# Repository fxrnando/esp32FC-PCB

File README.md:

# ESP32FC - PCB for X Quadcopter Drones

This repository contains the PCB designs and hardware documentation for a flight controller extension board based on the [esp-fc](https://github.com/rtlopez/esp-fc) project. The board is designed to connect an ESP32  microcontroller to a set of peripherals commonly used in unmanned aerial vehicles (UAVs) and robotics.

The project is intended to be developed using modular components commonly found in Arduino projects. This makes it easier for hobbyists to source and manipulate the parts, facilitating both assembly and PCB construction.

## 📦 Project Structure

The project contains two PCB versions:

* **v1-single-sided**: A one-layer PCB version, considered functional and stable, but not actively maintained.
**Note: This version has not yet been built or tested, as its dimensions are too large to fit inside the intended drone frame.**

* **v2-double-sided**: A two-layer PCB version, under active development, with continuous improvements and upgrades.

## 🧩 Features

* **Microcontroller**: ESP-WROOM-32 - ESP32 D1 Mini DevKit
* **IMU & Barometer**: SPI connection to MPU9250 and BMP250 (separated modules)
* **Motor Outputs**: 4 motor outputs, supporting PWM, Oneshot and DShot protocols
* **Serial Interfaces**:

  * `Serial1`: USB-to-serial for configuration (through Betaflight Configurator)
  * `Serial2`: Connection to ELRS receiver (CRSF protocol)
  * `Serial3`: Optional GPS or other peripheral like vtx smart audio (still not implemented in version 0.2.1)
* **Battery Monitoring**: Voltage divider for battery voltage measurement
* **Status Indication**: Piezo buzzer
* **Power Inputs**: LiPo battery connector
* **Power Outputs**:

  * ESCs power lines
  * Companion computer (e.g., Jetson Nano)

The board is designed to be installed in a standard F450 X-frame drone, but may also be adapted to fit other drone models with minor modifications.

## 📷 General Connections Diagram

Below is a visual representation of the wiring and placement of components for the quadcopter configuration using the ESP32FC board:

Legend:
* Yellow components: Electronic Speed Controllers (ESCs)
* Orange components: Brushless motors
* Center green board: ESP32FC custom PCB
* Black antenna: ELRS receiver module

All motor ESC signal wires are routed to the motor control pins on the PCB, while power and telemetry signals are handled via separate connections to the battery and optional modules.

## 🗂 Folder Overview

```text
hardware/                  PCB designs
  └── v1-single-sided/     Single-layer version
  └── v2-double-sided/     Dual-layer version
        └── exports/       3d images, BOM, g 
        └── kicad_pcb/    
  └── library/             Custom symbols & footprints
firmware/                  Optional test or support code
  └── ...
docs/                      Diagrams and usage docs and files
tools/                     Scripts for BOM or Gerber generation
```

## 🔧 Development

All initial configuration for the ESP32 module should be done following the instructions provided by @rtlopez in his esp-fc repository. This includes flashing the firmware, setting up the environment, and configuring the board.

Pin remapping specific to this board design (e.g., motor outputs, SPI, UARTs, battery monitor, buzzer) should be defined according to the layout described in the firmware/ section of this repository. Additional notes and configuration tips will be included there as development progresses.

All PCB designs are created using KiCad 9. Exports include Gerbers, BOMs, and 3D renders. Contributions are welcome, especially to the v2-double-sided version.

## 📝 License

This project is licensed under the **GPLv3**, following the upstream [esp-fc](https://github.com/rtlopez/esp-fc) licensing terms.

## 👤 Author & Maintainer

Developed and maintained by fxrnando. Based on the work of [@rtlopez](https://github.com/rtlopez).

---

Feel free to fork, modify, or contribute improvements to the hardware. If you build one, let us know!

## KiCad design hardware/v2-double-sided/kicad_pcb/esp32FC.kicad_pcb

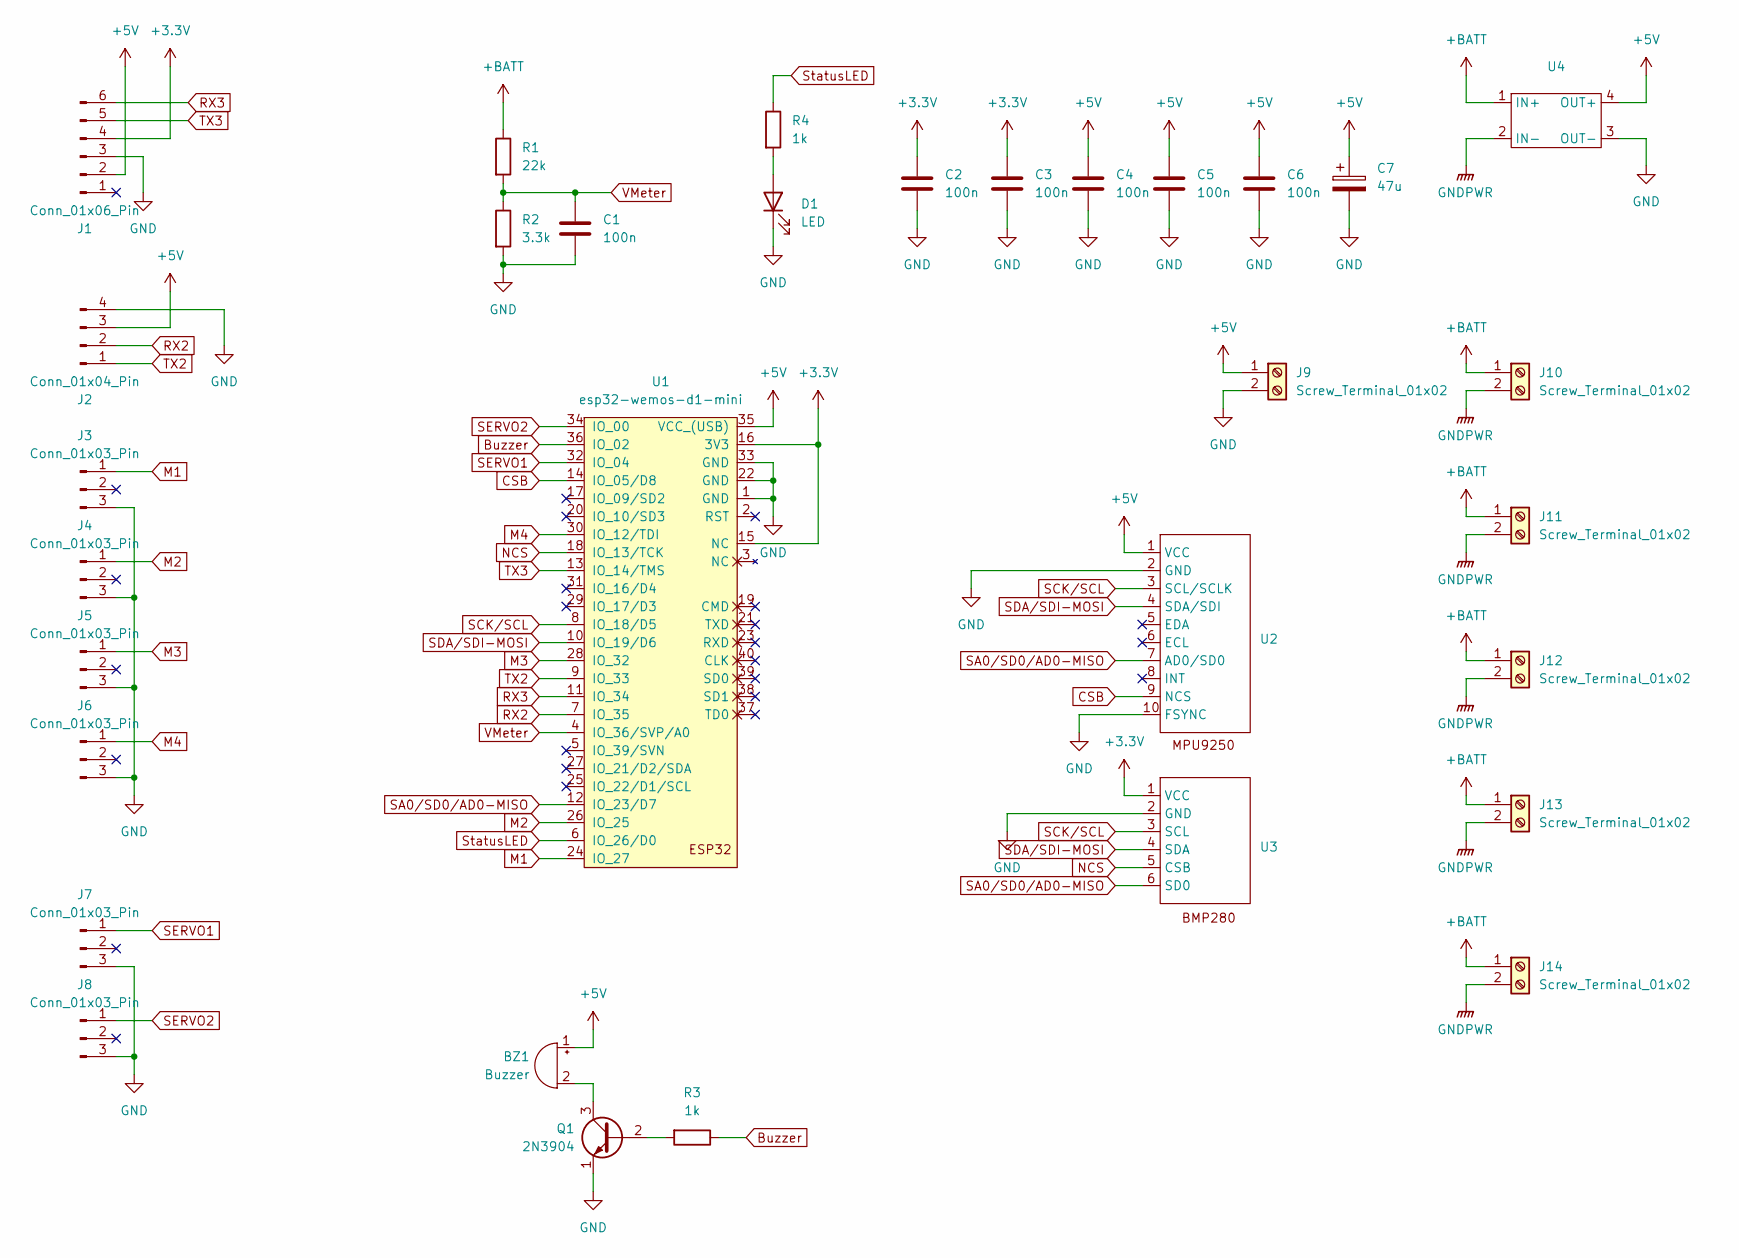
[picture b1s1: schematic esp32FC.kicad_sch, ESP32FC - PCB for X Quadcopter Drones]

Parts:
BZ1: Buzzer; Buzzer_12x9.5RM7.6
C1, C2, C3, C4, C5, C6: 100n; C_Disc_D3.8mm_W2.6mm_P2.50mm
C7: 47u; C_Radial_D10.0mm_H12.5mm_P5.00mm
D1: LED; LED_D3.0mm_Clear
J1: Conn_01x06_Pin; Molex_KK-254_AE-6410-06A_1x06_P2.54mm_Vertical
J2: Conn_01x04_Pin; Molex_KK-254_AE-6410-04A_1x04_P2.54mm_Vertical
J3, J4, J5, J6, J7, J8: Conn_01x03_Pin; PinHeader_1x03_P2.54mm_Vertical
J9, J10, J11, J12, J13, J14: Screw_Terminal_01x02; SolderWire-2.5sqmm_1x02_P8.8mm_D2.4mm_OD4.4mm
Q1: 2N3904; TO-92_Inline_Wide
R1: 22k; R_Axial_DIN0309_L9.0mm_D3.2mm_P2.54mm_Vertical
R2: 3.3k; R_Axial_DIN0309_L9.0mm_D3.2mm_P2.54mm_Vertical
R3: 1k; R_Axial_DIN0309_L9.0mm_D3.2mm_P2.54mm_Vertical
R4: 1k; R_Axial_DIN0207_L6.3mm_D2.5mm_P10.16mm_Horizontal
U1: esp32-wemos-d1-mini
U2: mpu9250
U3: bmp280
U4: xl4005 DC-DC stepdown module

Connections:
+3.3V: C2.1, C3.1, J1.4, U1.15 (NC), U1.16 (3V3), U3.1 (VCC)
+5V: BZ1.1 (+), C4.1, C5.1, C6.1, C7.1, J1.2, J2.3, J9.1, U1.35 (VCC_(USB)), U2.1 (VCC), U4.4 (OUT+)
+BATT: J10.1, J11.1, J12.1, J13.1, J14.1, R1.1, U4.1 (IN+)
Buzzer: R3.1, U1.36 (IO_02)
CSB: U1.14 (IO_05/D8), U2.9 (NCS)
GND: C1.2, C2.2, C3.2, C4.2, C5.2, C6.2, C7.2, D1.1 (K), J1.3, J2.4, J3.3, J4.3, J5.3, J6.3, J7.3, J8.3, J9.2, Q1.1 (E), R2.2, U1.1 (GND), U1.22 (GND), U1.33 (GND), U2.2 (GND), U2.10 (FSYNC), U3.2 (GND), U4.3 (OUT-)
GNDPWR: J10.2, J11.2, J12.2, J13.2, J14.2, U4.2 (IN-)
M1: J3.1, U1.24 (IO_27)
M2: J4.1, U1.26 (IO_25)
M3: J5.1, U1.28 (IO_32)
M4: J6.1, U1.30 (IO_12/TDI)
NCS: U1.18 (IO_13/TCK), U3.5 (CSB)
unnamed: BZ1.2 (-), Q1.3 (C)
unnamed: D1.2 (A), R4.2
unnamed: Q1.2 (B), R3.2
RX2: J2.2, U1.7 (IO_35)
RX3: J1.6, U1.11 (IO_34)
SA0/SD0/AD0-MISO: U1.12 (IO_23/D7), U2.7 (AD0/SD0), U3.6 (SD0)
SCK/SCL: U1.8 (IO_18/D5), U2.3 (SCL/SCLK), U3.3 (SCL)
SDA/SDI-MOSI: U1.10 (IO_19/D6), U2.4 (SDA/SDI), U3.4 (SDA)
SERVO1: J7.1, U1.32 (IO_04)
SERVO2: J8.1, U1.34 (IO_00)
StatusLED: R4.1, U1.6 (IO_26/D0)
TX2: J2.1, U1.9 (IO_33)
TX3: J1.5, U1.13 (IO_14/TMS)
VMeter: C1.1, R1.2, R2.1, U1.4 (IO_36/SVP/A0)

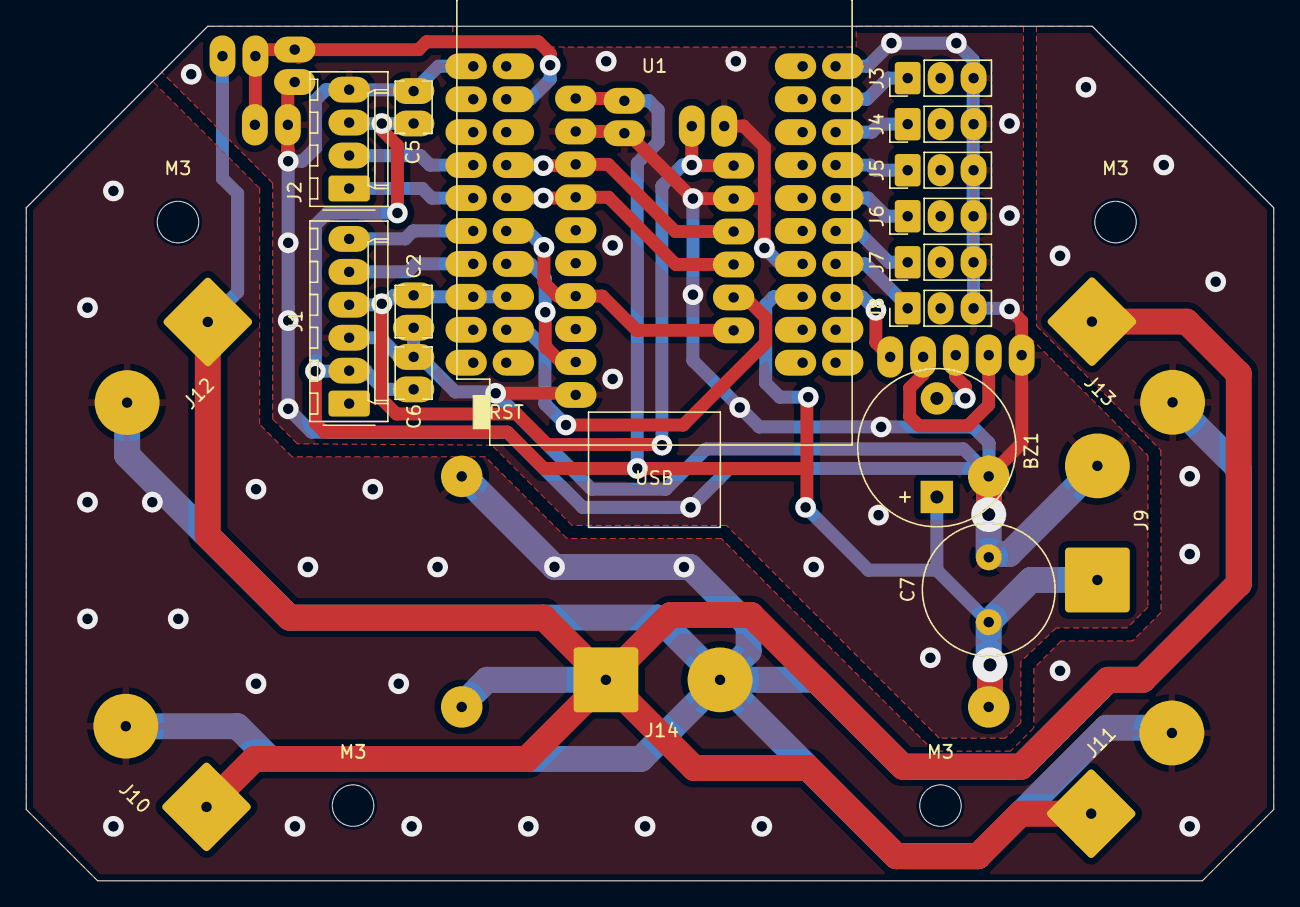
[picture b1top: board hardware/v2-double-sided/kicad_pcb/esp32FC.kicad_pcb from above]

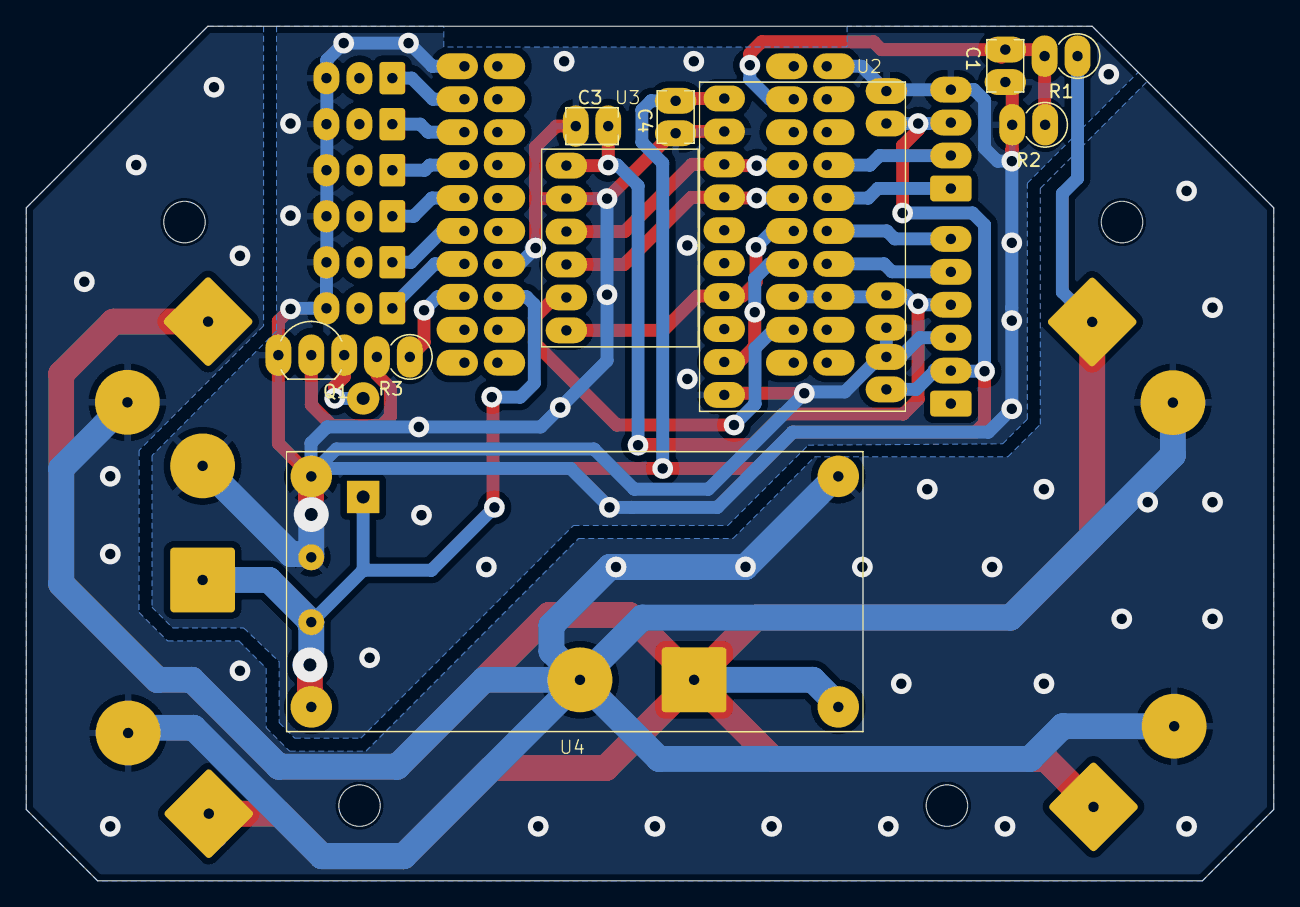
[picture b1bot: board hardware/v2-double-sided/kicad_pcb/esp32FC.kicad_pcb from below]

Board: 2 copper layers, 96.2 x 65.9 mm, 34 parts (10 on the bottom side), 24 nets.

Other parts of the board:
M3, M3#2, M3#3, M3#4: MountingHole_3.2mm_M3

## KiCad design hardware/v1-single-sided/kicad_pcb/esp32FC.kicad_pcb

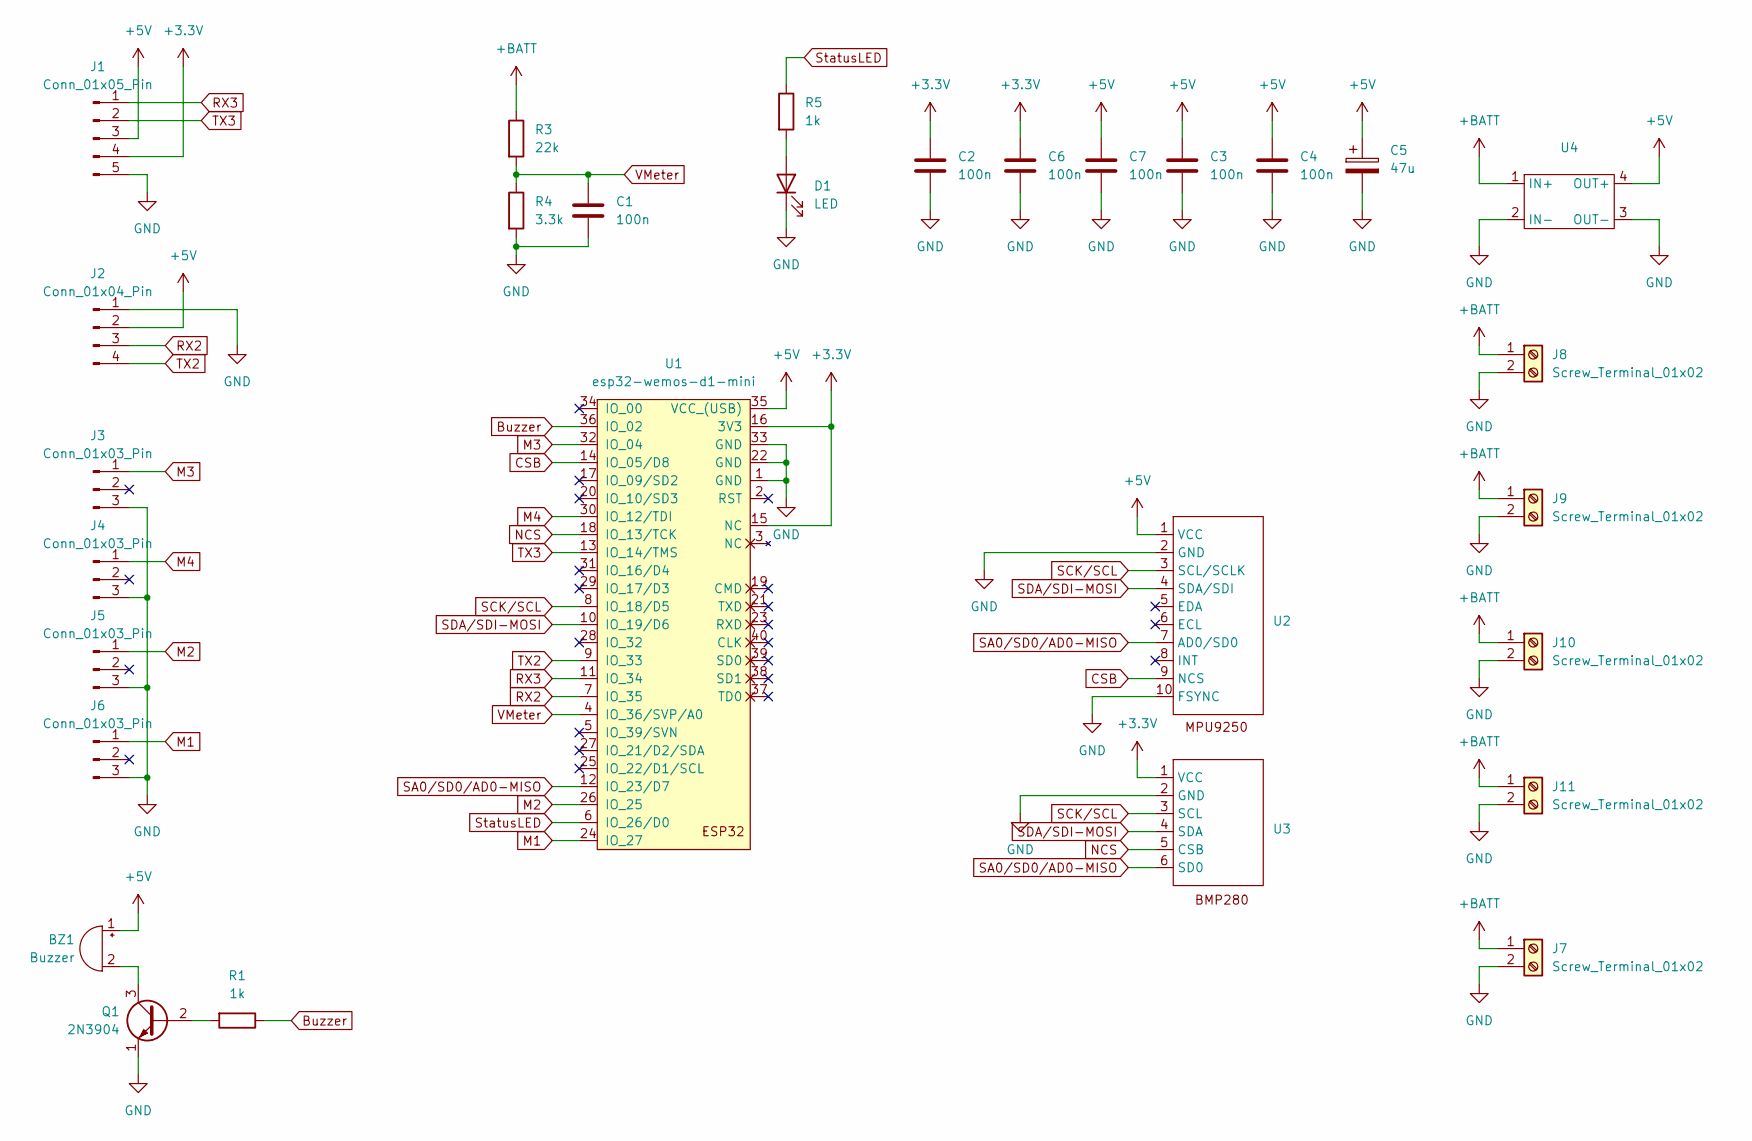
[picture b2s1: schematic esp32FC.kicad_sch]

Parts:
BZ1: Buzzer; Buzzer_12x9.5RM7.6
C1, C2, C3, C4, C6, C7: 100n; C_Axial_L3.8mm_D2.6mm_P7.50mm_Horizontal
C5: 47u; CP_Radial_Tantal_D7.0mm_P5.00mm
D1: LED; LED_D3.0mm_Clear
J1: Conn_01x05_Pin; PinHeader_1x05_P2.54mm_Vertical
J2: Conn_01x04_Pin; PinHeader_1x04_P2.54mm_Vertical
J3, J4, J5, J6: Conn_01x03_Pin; PinHeader_1x03_P2.54mm_Vertical
J7, J8, J9, J10, J11: Screw_Terminal_01x02; SolderWire-2.5sqmm_1x02_P8.8mm_D2.4mm_OD4.4mm
Q1: 2N3904; TO-92_Inline_Wide
R1: 1k; R_Axial_DIN0309_L9.0mm_D3.2mm_P2.54mm_Vertical
R3: 22k; R_Axial_DIN0207_L6.3mm_D2.5mm_P10.16mm_Horizontal
R4: 3.3k; R_Axial_DIN0309_L9.0mm_D3.2mm_P2.54mm_Vertical
R5: 1k; R_Axial_DIN0207_L6.3mm_D2.5mm_P10.16mm_Horizontal
U1: esp32-wemos-d1-mini
U2: mpu9250
U3: bmp280
U4: xl4005 DC-DC stepdown module

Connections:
+3.3V: C2.1, C6.1, J1.4, U1.15 (NC), U1.16 (3V3), U3.1 (VCC)
+5V: BZ1.1 (+), C3.1, C4.1, C5.1, C7.1, J1.3, J2.2, U1.35 (VCC_(USB)), U2.1 (VCC), U4.4 (OUT+)
+BATT: J7.1, J8.1, J9.1, J10.1, J11.1, R3.1, U4.1 (IN+)
Buzzer: R1.1, U1.36 (IO_02)
CSB: U1.14 (IO_05/D8), U2.9 (NCS)
GND: C1.2, C2.2, C3.2, C4.2, C5.2, C6.2, C7.2, D1.1 (K), J1.5, J2.1, J3.3, J4.3, J5.3, J6.3, J7.2, J8.2, J9.2, J10.2, J11.2, Q1.1 (E), R4.2, U1.1 (GND), U1.22 (GND), U1.33 (GND), U2.2 (GND), U2.10 (FSYNC), U3.2 (GND), U4.2 (IN-), U4.3 (OUT-)
M1: J6.1, U1.24 (IO_27)
M2: J5.1, U1.26 (IO_25)
M3: J3.1, U1.32 (IO_04)
M4: J4.1, U1.30 (IO_12/TDI)
NCS: U1.18 (IO_13/TCK), U3.5 (CSB)
unnamed: BZ1.2 (-), Q1.3 (C)
unnamed: D1.2 (A), R5.2
unnamed: Q1.2 (B), R1.2
RX2: J2.3, U1.7 (IO_35)
RX3: J1.1, U1.11 (IO_34)
SA0/SD0/AD0-MISO: U1.12 (IO_23/D7), U2.7 (AD0/SD0), U3.6 (SD0)
SCK/SCL: U1.8 (IO_18/D5), U2.3 (SCL/SCLK), U3.3 (SCL)
SDA/SDI-MOSI: U1.10 (IO_19/D6), U2.4 (SDA/SDI), U3.4 (SDA)
StatusLED: R5.1, U1.6 (IO_26/D0)
TX2: J2.4, U1.9 (IO_33)
TX3: J1.2, U1.13 (IO_14/TMS)
VMeter: C1.1, R3.2, R4.1, U1.4 (IO_36/SVP/A0)

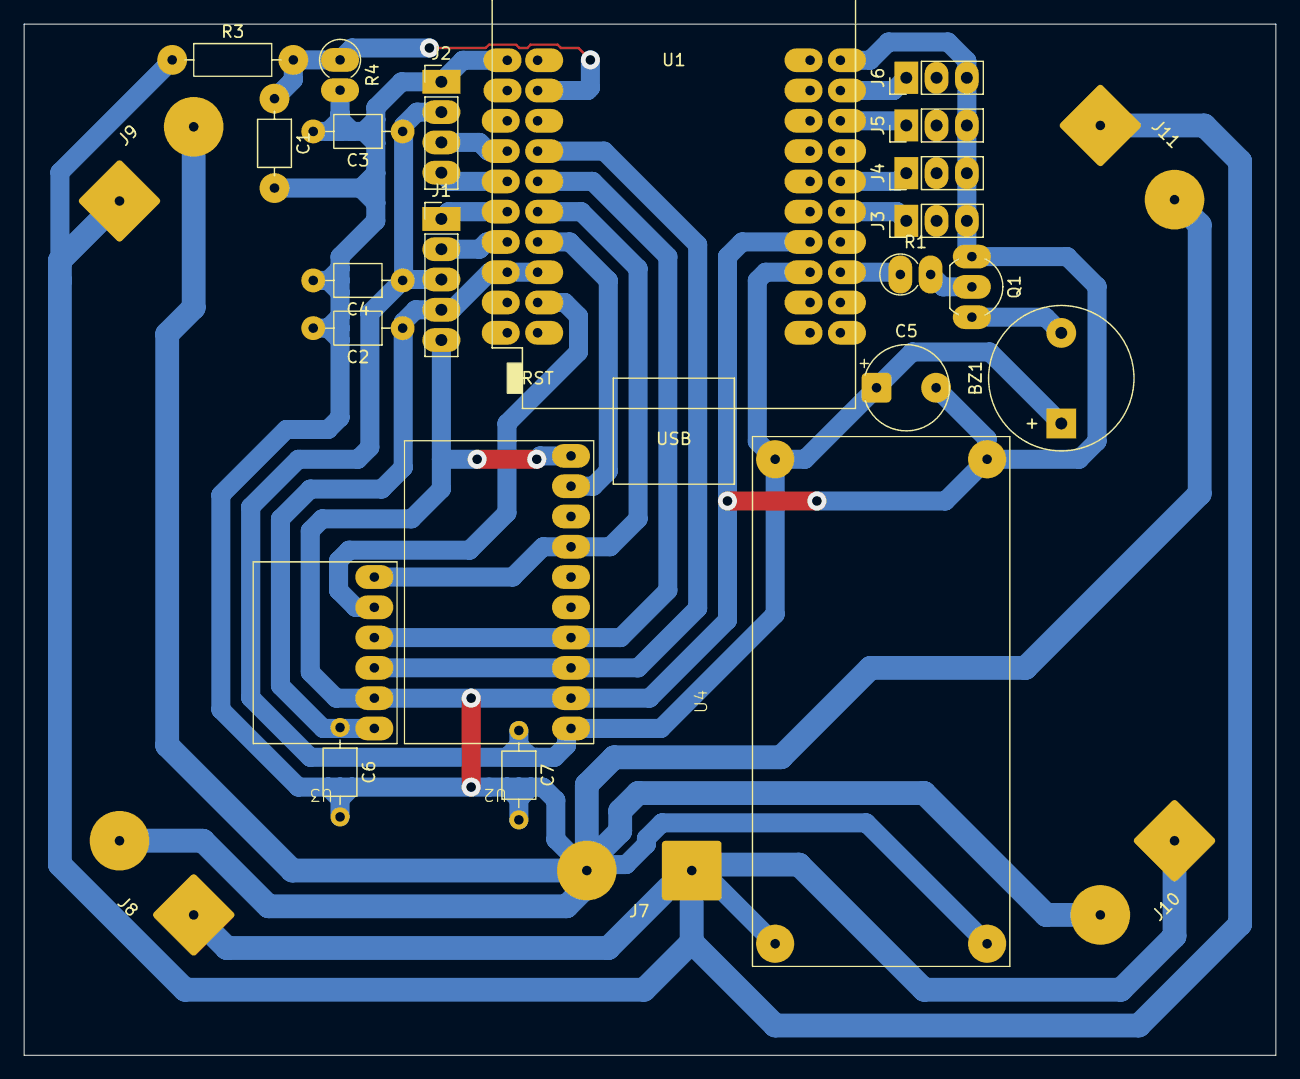
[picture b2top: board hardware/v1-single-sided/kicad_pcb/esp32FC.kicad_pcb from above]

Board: 2 copper layers, 105.0 x 86.5 mm, 27 parts (0 on the bottom side), 21 nets.

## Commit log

2025-06-28 Added first PCB version (1 sided one).
2025-06-28 Update LICENSE
2025-06-29 Updated readme and added exports for v1 PCB
2025-06-29 Created v2 PCB
2025-06-30 Added screw holes and export files
2025-07-01 Modified connectors for serial connections, now used molex connectors
2025-07-03 Updated README and added a general connections diagram
2025-07-13 Modified the PCB so it now has two ground layers instead of one power and one ground.
2025-07-14 Added two additional outs, to connect two additional servos
